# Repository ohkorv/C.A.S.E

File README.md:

<h1 align="center">
  <br>
  
  <br>
  C.A.S.E
  <br>
</h1>

<h4 align="center">
A sleek looking macropad
</h4>

<div align="center">

</div>

<div align="center">

</div>

# Project Details
C.A.S.E is a custom macropad made to fit my needs. It has 8 Baby Kangaroo Cherry MX Switches, a rotary encoder with a button usb c port and is powered by a esp32-s3.

# Repo  Structure
- `Libs/` Contains 3d models, symbols and footprints for Kicad
- `Blender/` It has the files neccesary for blender rendering.
- `Production/pcb` PCB fabrication files (Gerbers, BOM, Pick & Place)
- `Production/Case` F3d and step files of the custom case I made in Fusion 360
- `Renders/` Rendered pictures of the final product
- `Hardware/` Pcb and schematic from Kicad
- `Software/Companion App`  Companion app for controlling C.A.S.E
- `Software/MacroPad software`  Code to be put on the C.A.S.E

# Software Features
It has a easy to use companion app and is simple to setup. You simply assign actions to buttons. And have a python script running in the background.
Building the app is simple, just simply download it and download godot .net with it. Then compile it in the app. There are plenty of tutorials online if you are unsure

# Photo Gallery

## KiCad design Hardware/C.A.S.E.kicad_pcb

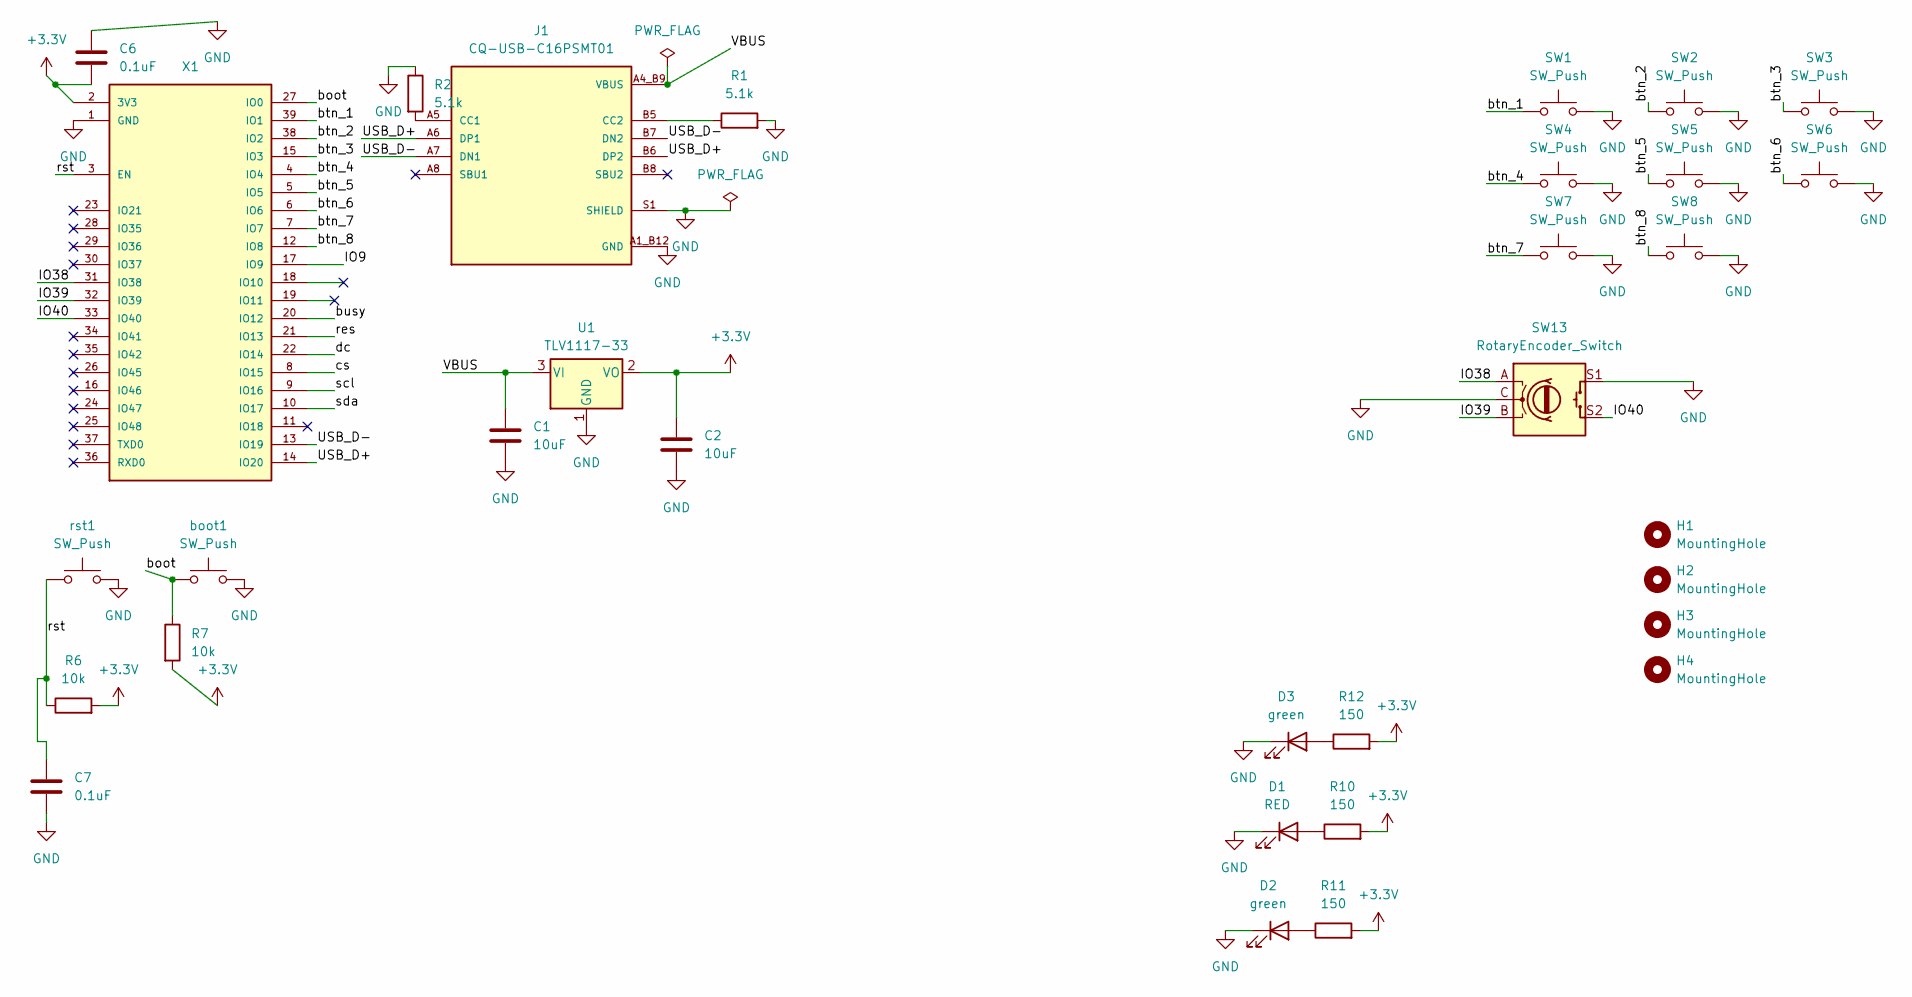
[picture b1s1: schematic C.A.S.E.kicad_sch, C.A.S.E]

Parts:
C1, C2: 10uF; C_0805_2012Metric
C6, C7: 0.1uF; C_0805_2012Metric
D1: RED; LED_0805_2012Metric
D2, D3: green; LED_0805_2012Metric
H1, H2, H3, H4: MountingHole; MountingHole_2.2mm_M2_Pad
J1: CQ-USB-C16PSMT01; SHENZHEN-CHUANGQIN-TECHNOLOGY_CQ-USB-C16PSMT01; PARTREV A
R1, R2: 5.1k; R_0805_2012Metric
R6, R7: 10k; R_0805_2012Metric
R10, R11, R12: 150; R_0805_2012Metric
SW1, SW2, SW3, SW4, SW5, SW6, SW7, SW8: SW_Push; SW_Cherry_MX_1.00u_PCB
SW13: RotaryEncoder_Switch; RotaryEncoder_Alps_EC11E-Switch_Vertical_H20mm
U1: TLV1117-33; SOT230P700X180-4N
X1: ESP32-S3-WROOM-1-N16R8; ESP32S3WROOM1N8R2; MANUFACTURER_PART_NUMBER ESP32-S3-WROOM-1-N16R8
boot1: SW_Push; 434121025816
rst1: SW_Push; 434121025816

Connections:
+3.3V: C2.1, C6.2, R6.2, R7.2, R10.2, R11.2, R12.2, U1.2 (VO), X1.2 (3V3)
/IO9: X1.17 (IO9)
/IO38: SW13.A, X1.31 (IO38)
/IO39: SW13.B, X1.32 (IO39)
/IO40: SW13.S2, X1.33 (IO40)
/USB_D+: J1.A6 (DP1), J1.B6 (DP2), X1.14 (IO20)
/USB_D-: J1.A7 (DN1), J1.B7 (DN2), X1.13 (IO19)
/boot: R7.1, X1.27 (IO0), boot1.1; also elsewhere on the board
/btn_1: SW1.1, X1.39 (IO1)
/btn_2: SW2.1, X1.38 (IO2)
/btn_3: SW3.1, X1.15 (IO3)
/btn_4: SW4.1, X1.4 (IO4)
/btn_5: SW5.1, X1.5 (IO5)
/btn_6: SW6.1, X1.6 (IO6)
/btn_7: SW7.1, X1.7 (IO7)
/btn_8: SW8.1, X1.12 (IO8)
/busy: X1.20 (IO12)
/cs: X1.8 (IO15)
/dc: X1.22 (IO14)
/res: X1.21 (IO13)
/rst: C7.2, R6.1, X1.3 (EN), rst1.1; also elsewhere on the board
/scl: X1.9 (IO16)
/sda: X1.10 (IO17)
GND: C1.2, C2.2, C6.1, C7.1, D1.1 (K), D2.1 (K), D3.1 (K), J1.A1_B12 (GND), J1.B1_A12 (GND), J1.S1 (SHIELD), J1.S2 (SHIELD), J1.S3 (SHIELD), J1.S4 (SHIELD), R1.2, R2.1, SW1.2, SW2.2, SW3.2, SW4.2, SW5.2, SW6.2, SW7.2, SW8.2, SW13.C, SW13.S1, U1.1 (GND), X1.1 (GND), X1.40 (GND), X1.41 (GND), X1.42 (GND), X1.43 (GND), X1.44 (GND), X1.45 (GND), X1.46 (GND), X1.47 (GND), X1.48 (GND), X1.49 (GND), boot1.2, rst1.2; also elsewhere on the board
unnamed: D1.2 (A), R10.1
unnamed: D2.2 (A), R11.1
unnamed: D3.2 (A), R12.1
unnamed: J1.A5 (CC1), R2.2
unnamed: J1.B5 (CC2), R1.1
VBUS: C1.1, J1.A4_B9 (VBUS), J1.B4_A9 (VBUS), U1.3 (VI)

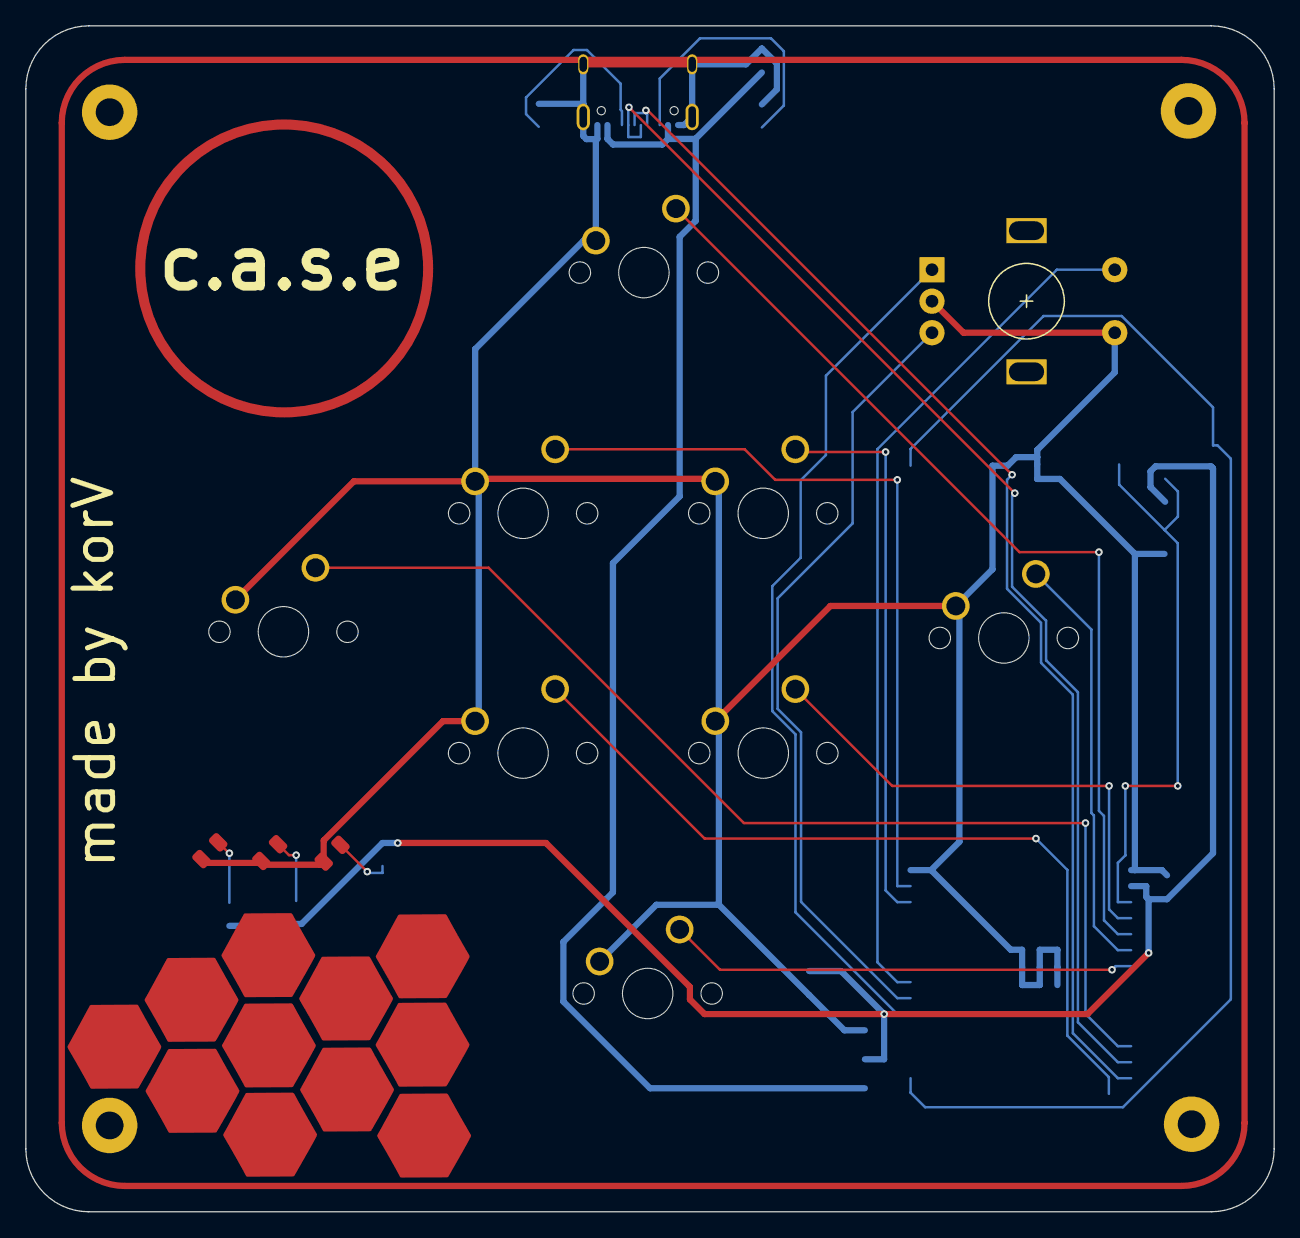
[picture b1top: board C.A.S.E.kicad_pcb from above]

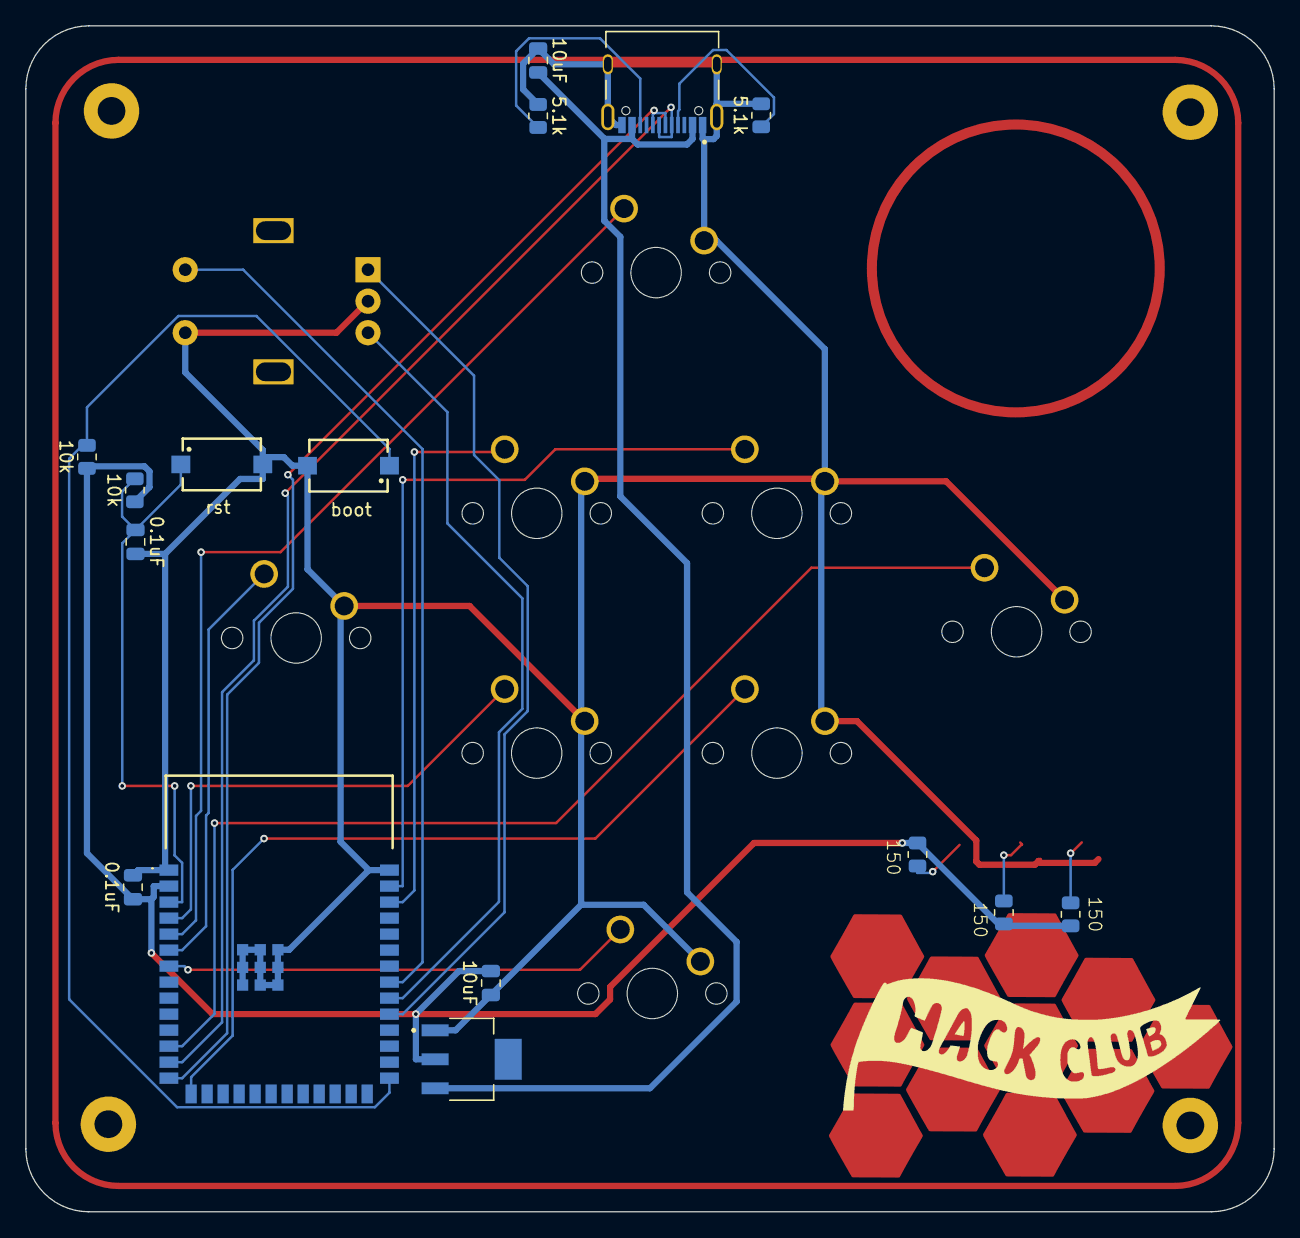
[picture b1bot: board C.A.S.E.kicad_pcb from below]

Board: 2 copper layers, 99.0 x 94.1 mm, 32 parts (16 on the bottom side), 23 nets.

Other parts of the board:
boot: SW_Push; 434121025816
rst: SW_Push; 434121025816

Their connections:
/boot: boot.1; also elsewhere on the board
/rst: rst.1; also elsewhere on the board
GND: boot.2, rst.2; also elsewhere on the board

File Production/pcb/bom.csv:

Designator,Footprint,Quantity,Value,LCSC Part #
"BOOT, RST",434121025816,2,SW_Push,
"C1, C2",0805,2,10uF,
"C6, C7",0805,2,0.1uF,
D1,0805,1,RED,
"D2, D3",0805,2,green,
J1,SHENZHEN-CHUANGQIN-TECHNOLOGY_CQ-USB-C16PSMT01,1,CQ-USB-C16PSMT01,
"R1, R2",0805,2,5.1k,
"R10, R11, R12",0805,3,150,
"R6, R7",0805,2,10k,
"SW1, SW2, SW3, SW4, SW5, SW6, SW7, SW8",SW_Cherry_MX_1.00u_PCB,8,SW_Push,
SW13,RotaryEncoder_Alps_EC11E-Switch_Vertical_H20mm,1,RotaryEncoder_Switch,
U1,SOT230P700X180-4N,1,TLV1117-33,
X1,ESP32S3WROOM1N8R2,1,ESP32-S3-WROOM-1-N16R8,

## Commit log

2026-06-02 adding more stuff
2026-06-05 changed everything
2026-06-05 Replace project title with animated SVG
    Updated project title with a typing SVG animation.
2026-06-05 Add new typing SVG to README
    Updated the README to include a new typing SVG.
2026-06-06 some stuff
2026-06-06 good
2026-06-07 added the companion app
2026-06-07 Update README with project title and description
2026-06-07 Insert project image in README
    Add project image to README with center alignment
2026-06-07 Update README with project details and structure
    Added project details and repository structure sections to README.
2026-06-07 cleaned up the repo
2026-06-08 companion app fixes
2026-06-08 Enhance README with software features and images
    Added sections for software features and photo gallery.
2026-06-08 Add additional images to README
2026-06-10 Improve README clarity and fix grammar
    Fixed grammatical errors and improved clarity in the README.

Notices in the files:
README.md:
License: MIT
